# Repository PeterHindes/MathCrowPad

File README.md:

# MathCrowPad

## The MathCrowPad is a numberpad for chemistry, math, and spreadsheets.

Its main three features are:
 * Two knobs to scroll through spreadsheets
 * An oled screen to show guides for the knobs
 * An extra row for parenthisis(), exponent^, factorial!, latex syntax$$ etc.

Feel free to make up to 10 for personal use.

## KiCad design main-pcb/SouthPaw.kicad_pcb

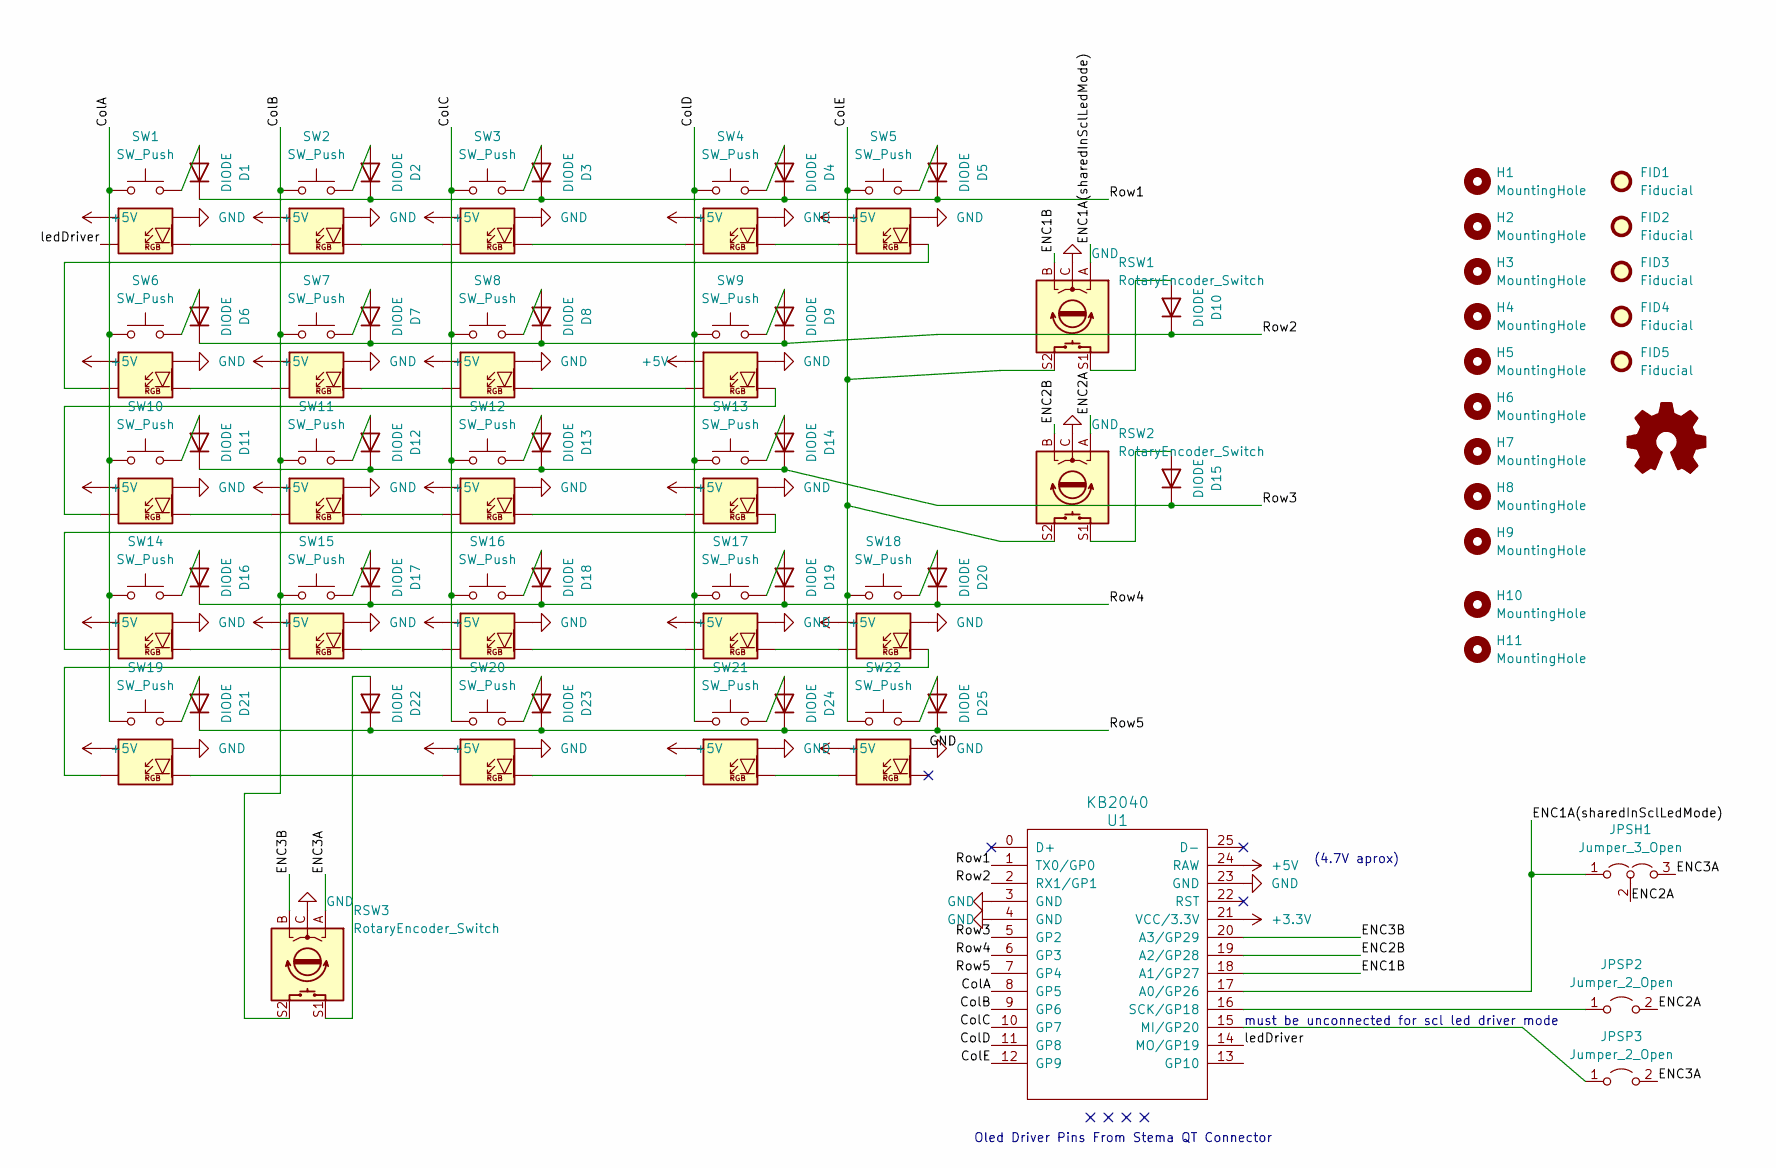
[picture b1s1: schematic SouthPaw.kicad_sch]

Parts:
D1, D2, D3, D4, D5, D6, D7, D8, D9, D10, D11, D12, D13, D14, D15, D16, D17, D18, D19, D20, D21, D22, D23, D24, D25: DIODE; Diode-dual
FID1, FID2, FID3, FID4, FID5: Fiducial; Fiducial_0.5mm_Mask1mm
H1: MountingHole; 0.91in 128x32 I2C STEMMA QT standoff only with cutout
H2, H3, H4, H5, H6, H7, H8, H9, H10, H11: MountingHole; m2.5 hole
JPSH1: Jumper_3_Open; SolderJumper-3_P2.0mm_Open_TrianglePad1.0x1.5mm
JPSP2, JPSP3: Jumper_2_Open; SolderJumper-2_P1.3mm_Open_TrianglePad1.0x1.5mm
RSW1, RSW2, RSW3: RotaryEncoder_Switch; RotaryEncoder_EC11
SW1, SW2, SW3, SW4, SW5, SW6, SW7, SW8, SW9, SW10, SW11, SW12, SW13, SW14, SW15, SW16, SW17, SW19, SW21: SW_Push; SW_Cherry_MX_1.00u_PCB_WITH_SK6812MINI-E
SW18, SW20, SW22: SW_Push; SW_Cherry_MX_2.00u_PCB_WITH_SK6812MINI-E
U1: KB2040; KB2040 through hole only (top mount with hotpins 3d model v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

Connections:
+3.3V: U1.21 (VCC/3.3V)
+5V: SW1.21 (ledVDD), SW2.21 (ledVDD), SW3.21 (ledVDD), SW4.21 (ledVDD), SW5.21 (ledVDD), SW6.21 (ledVDD), SW7.21 (ledVDD), SW8.21 (ledVDD), SW9.21 (ledVDD), SW10.21 (ledVDD), SW11.21 (ledVDD), SW12.21 (ledVDD), SW13.21 (ledVDD), SW14.21 (ledVDD), SW15.21 (ledVDD), SW16.21 (ledVDD), SW17.21 (ledVDD), SW18.21 (ledVDD), SW19.21 (ledVDD), SW20.21 (ledVDD), SW21.21 (ledVDD), SW22.21 (ledVDD), U1.24 (RAW)
/ColA: SW1.11 (sw1), SW6.11 (sw1), SW10.11 (sw1), SW14.11 (sw1), SW19.11 (sw1), U1.8 (GP5)
/ColB: RSW3.S2, SW2.11 (sw1), SW7.11 (sw1), SW11.11 (sw1), SW15.11 (sw1), U1.9 (GP6)
/ColC: SW3.11 (sw1), SW8.11 (sw1), SW12.11 (sw1), SW16.11 (sw1), SW20.11 (sw1), U1.10 (GP7)
/ColD: SW4.11 (sw1), SW9.11 (sw1), SW13.11 (sw1), SW17.11 (sw1), SW21.11 (sw1), U1.11 (GP8)
/ColE: RSW1.S2, RSW2.S2, SW5.11 (sw1), SW18.11 (sw1), SW22.11 (sw1), U1.12 (GP9)
/ENC1A(sharedInSclLedMode): JPSH1.1 (A), RSW1.A, U1.17 (A0/GP26)
/ENC1B: RSW1.B, U1.18 (A1/GP27)
/ENC2A: JPSH1.2 (C), JPSP2.2 (B), RSW2.A
/ENC2B: RSW2.B, U1.19 (A2/GP28)
/ENC3A: JPSH1.3 (B), JPSP3.2 (B), RSW3.A
/ENC3B: RSW3.B, U1.20 (A3/GP29)
/Row1: D1.2 (K), D2.2 (K), D3.2 (K), D4.2 (K), D5.2 (K), U1.1 (TX0/GP0)
/Row2: D6.2 (K), D7.2 (K), D8.2 (K), D9.2 (K), D10.2 (K), U1.2 (RX1/GP1)
/Row3: D11.2 (K), D12.2 (K), D13.2 (K), D14.2 (K), D15.2 (K), U1.5 (GP2)
/Row4: D16.2 (K), D17.2 (K), D18.2 (K), D19.2 (K), D20.2 (K), U1.6 (GP3)
/Row5: D21.2 (K), D22.2 (K), D23.2 (K), D24.2 (K), D25.2 (K), U1.7 (GP4)
/ledDriver: SW1.24 (ledDIN), U1.14 (MO/GP19)
GND: RSW1.C, RSW2.C, RSW3.C, SW1.23 (ledGND), SW2.23 (ledGND), SW3.23 (ledGND), SW4.23 (ledGND), SW5.23 (ledGND), SW6.23 (ledGND), SW7.23 (ledGND), SW8.23 (ledGND), SW9.23 (ledGND), SW10.23 (ledGND), SW11.23 (ledGND), SW12.23 (ledGND), SW13.23 (ledGND), SW14.23 (ledGND), SW15.23 (ledGND), SW16.23 (ledGND), SW17.23 (ledGND), SW18.23 (ledGND), SW19.23 (ledGND), SW20.23 (ledGND), SW21.23 (ledGND), SW22.23 (ledGND), U1.3 (GND), U1.4 (GND), U1.23 (GND)
unnamed: D1.1 (A), SW1.12 (sw2)
unnamed: D2.1 (A), SW2.12 (sw2)
unnamed: D3.1 (A), SW3.12 (sw2)
unnamed: D4.1 (A), SW4.12 (sw2)
unnamed: D5.1 (A), SW5.12 (sw2)
unnamed: D6.1 (A), SW6.12 (sw2)
unnamed: D7.1 (A), SW7.12 (sw2)
unnamed: D8.1 (A), SW8.12 (sw2)
unnamed: D9.1 (A), SW9.12 (sw2)
unnamed: D10.1 (A), RSW1.S1
unnamed: D11.1 (A), SW10.12 (sw2)
unnamed: D12.1 (A), SW11.12 (sw2)
unnamed: D13.1 (A), SW12.12 (sw2)
unnamed: D14.1 (A), SW13.12 (sw2)
unnamed: D15.1 (A), RSW2.S1
unnamed: D16.1 (A), SW14.12 (sw2)
unnamed: D17.1 (A), SW15.12 (sw2)
unnamed: D18.1 (A), SW16.12 (sw2)
unnamed: D19.1 (A), SW17.12 (sw2)
unnamed: D20.1 (A), SW18.12 (sw2)
unnamed: D21.1 (A), SW19.12 (sw2)
unnamed: D22.1 (A), RSW3.S1
unnamed: D23.1 (A), SW20.12 (sw2)
unnamed: D24.1 (A), SW21.12 (sw2)
unnamed: D25.1 (A), SW22.12 (sw2)
unnamed: JPSP2.1 (A), U1.16 (SCK/GP18)
unnamed: JPSP3.1 (A), U1.15 (MI/GP20)
unnamed: SW1.22 (ledDOUT), SW2.24 (ledDIN)
unnamed: SW2.22 (ledDOUT), SW3.24 (ledDIN)
unnamed: SW3.22 (ledDOUT), SW4.24 (ledDIN)
unnamed: SW4.22 (ledDOUT), SW5.24 (ledDIN)
unnamed: SW5.22 (ledDOUT), SW6.24 (ledDIN)
unnamed: SW6.22 (ledDOUT), SW7.24 (ledDIN)
unnamed: SW7.22 (ledDOUT), SW8.24 (ledDIN)
unnamed: SW8.22 (ledDOUT), SW9.24 (ledDIN)
unnamed: SW10.22 (ledDOUT), SW11.24 (ledDIN)
unnamed: SW9.22 (ledDOUT), SW10.24 (ledDIN)
unnamed: SW11.22 (ledDOUT), SW12.24 (ledDIN)
unnamed: SW12.22 (ledDOUT), SW13.24 (ledDIN)
unnamed: SW13.22 (ledDOUT), SW14.24 (ledDIN)
unnamed: SW14.22 (ledDOUT), SW15.24 (ledDIN)
unnamed: SW15.22 (ledDOUT), SW16.24 (ledDIN)
unnamed: SW16.22 (ledDOUT), SW17.24 (ledDIN)
unnamed: SW17.22 (ledDOUT), SW18.24 (ledDIN)
unnamed: SW18.22 (ledDOUT), SW19.24 (ledDIN)
unnamed: SW19.22 (ledDOUT), SW20.24 (ledDIN)
unnamed: SW20.22 (ledDOUT), SW21.24 (ledDIN)
unnamed: SW21.22 (ledDOUT), SW22.24 (ledDIN)

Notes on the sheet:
Oled Driver Pins From Stema QT Connector
must be unconnected for scl led driver mode
(4.7V aprox)

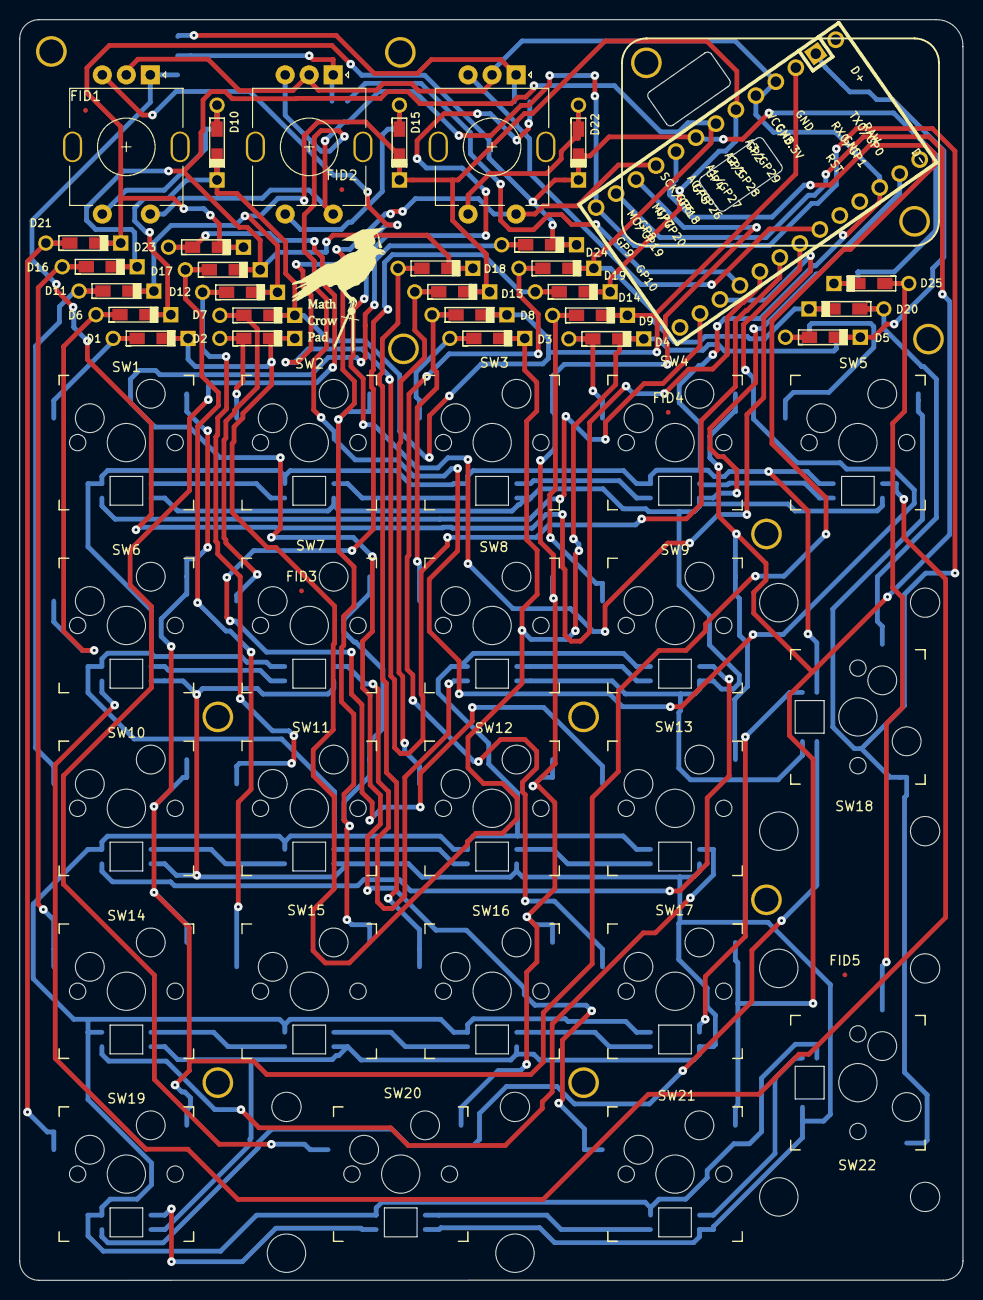
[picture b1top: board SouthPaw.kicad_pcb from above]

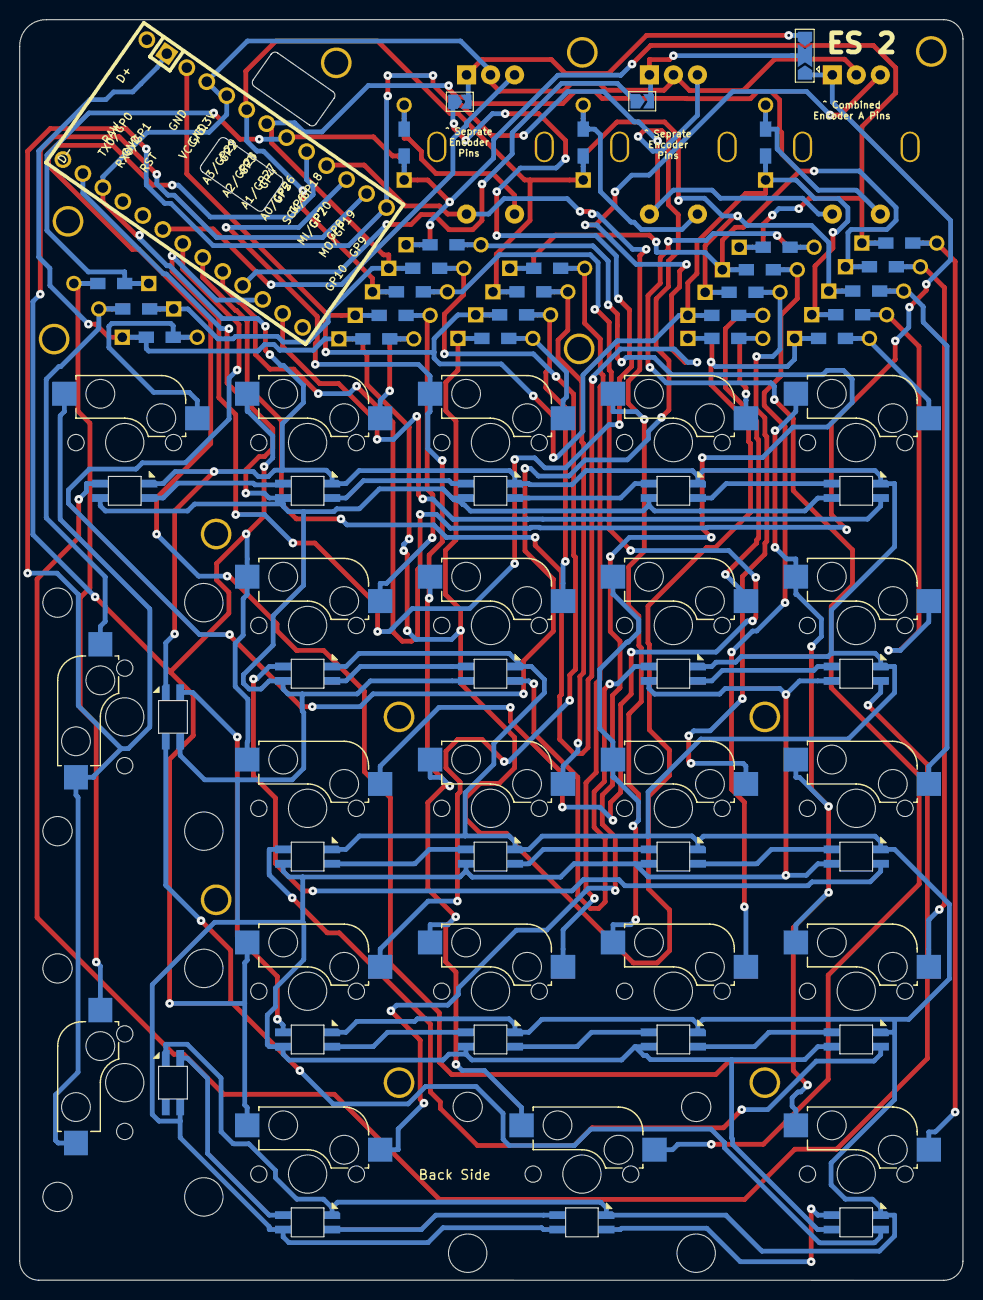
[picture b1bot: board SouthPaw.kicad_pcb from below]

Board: 2 copper layers, 98.2 x 131.3 mm, 70 parts (3 on the bottom side), 67 nets.

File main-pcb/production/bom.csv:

Designator,Footprint,Quantity,Value,LCSC Part #
"D1, D10, D11, D12, D13, D14, D15, D16, D17, D18, D19, D2, D20, D21, D22, D23, D24, D25, D3, D4, D5, D6, D7, D8, D9",Diode-dual,25,DIODE,
FID1,Fiducial_0.5mm_Mask1mm,1,Fiducial,
JPSH1,SolderJumper-3_P2.0mm_Open_TrianglePad1.0x1.5mm,1,Jumper_3_Open,
"JPSP2, JPSP3",SolderJumper-2_P1.3mm_Open_TrianglePad1.0x1.5mm,2,Jumper_2_Open,
"RSW1, RSW2, RSW3",RotaryEncoder_EC11,3,RotaryEncoder_Switch,
"SW1, SW10, SW11, SW12, SW13, SW14, SW15, SW16, SW17, SW19, SW2, SW21, SW3, SW4, SW5, SW6, SW7, SW8, SW9",SW_Cherry_MX_1.00u_PCB_WITH_SK6812MINI-E,19,SW_Push,
"SW18, SW20, SW22",SW_Cherry_MX_2.00u_PCB_WITH_SK6812MINI-E,3,SW_Push,
U1,KB2040 through hole only (top mount with hotpins 3d model view),1,KB2040,

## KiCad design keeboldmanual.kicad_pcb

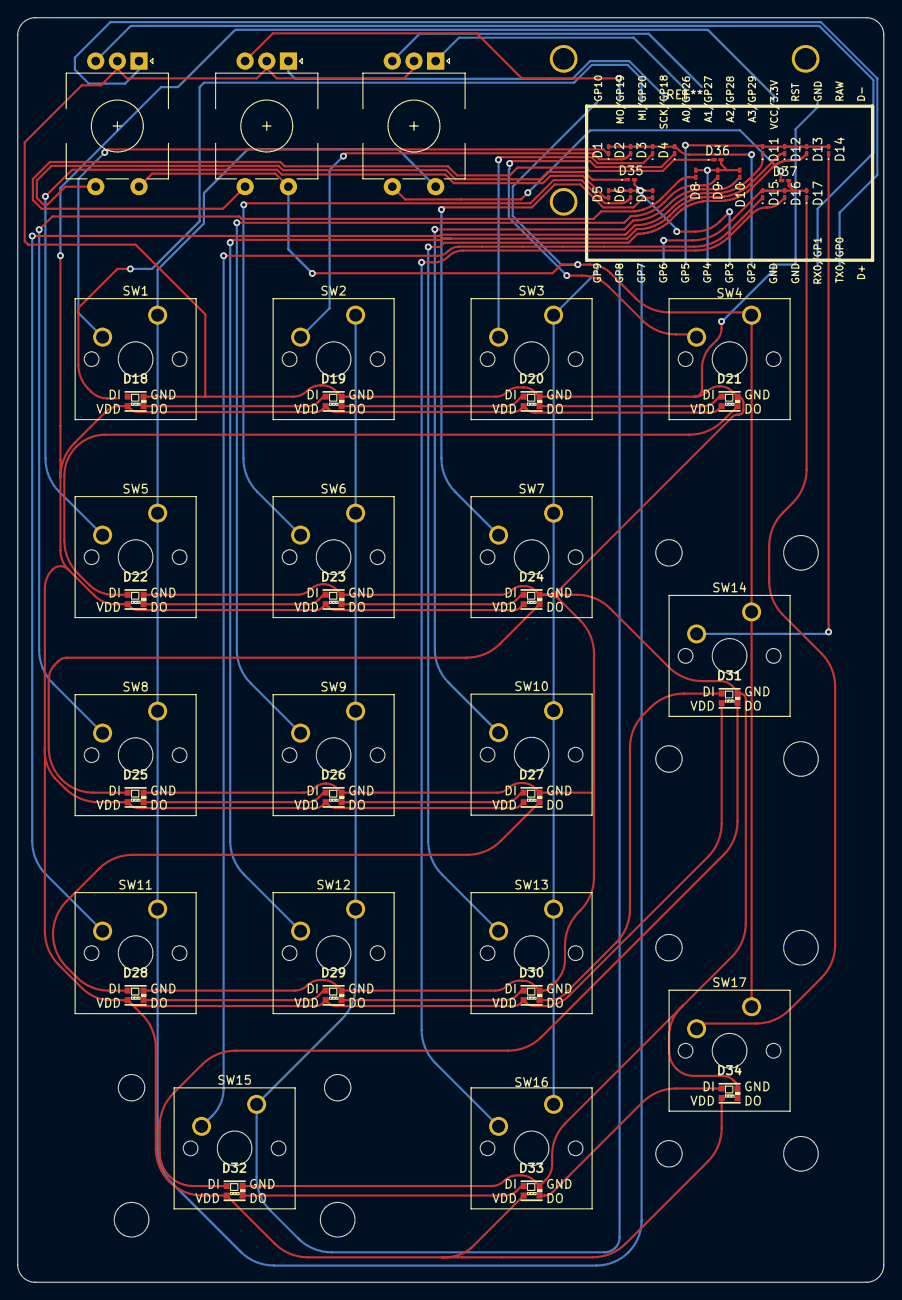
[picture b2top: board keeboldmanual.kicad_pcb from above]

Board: 2 copper layers, 100.0 x 146.0 mm, 58 parts (1 on the bottom side), 54 nets.

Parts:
D1, D2, D3, D4, D5, D6, D7, D8, D9, D10, D11, D12, D13, D14, D15, D16, D17, D35, D36, D37: DIODE; D_0201_0603Metric_Pad0.64x0.40mm_HandSolder
D18, D19, D20, D21, D22, D23, D24, D25, D26, D27, D28, D29, D30, D31, D32, D33, D34: WS2812B_2mm; WS2812B 2mmx2.2mm version
SW1, SW2, SW3, SW4, SW5, SW6, SW7, SW8, SW9, SW10, SW11, SW12, SW13, SW16: SW_Push; SW_Cherry_MX_1.00u_PCB
SW14, SW17: SW_Push; SW_Cherry_MX_2.00u_Vertical_PCB
SW15: SW_Push; SW_Cherry_MX_2.00u_PCB
SW18, SW19, SW20: RotaryEncoder_Switch; RotaryEncoder_EC11
U1: KB2040; KB2040 (modified from Elite-C-castellated-24pin)

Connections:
/3.3V: D18.4 (VDD), D19.4 (VDD), D20.4 (VDD), D21.4 (VDD), D22.4 (VDD), D23.4 (VDD), D24.4 (VDD), D25.4 (VDD), D26.4 (VDD), D27.4 (VDD), D28.4 (VDD), D29.4 (VDD), D30.4 (VDD), D31.4 (VDD), D32.4 (VDD), D33.4 (VDD), D34.4 (VDD), U1.21 (VCC/3.3V)
/GND: D18.2 (GND), D19.2 (GND), D20.2 (GND), D21.2 (GND), D22.2 (GND), D23.2 (GND), D24.2 (GND), D25.2 (GND), D26.2 (GND), D27.2 (GND), D28.2 (GND), D29.2 (GND), D30.2 (GND), D31.2 (GND), D32.2 (GND), D33.2 (GND), D34.2 (GND), SW18.C, SW19.C, SW20.C, U1.3 (GND), U1.4 (GND), U1.23 (GND)
unnamed: D1.1 (A), SW1.2
unnamed: D1.2 (K), D2.2 (K), D3.2 (K), D4.2 (K), U1.5 (GP2)
unnamed: D2.1 (A), SW2.2
unnamed: D3.1 (A), SW3.2
unnamed: D4.1 (A), SW4.2
unnamed: D5.1 (A), SW5.2
unnamed: D5.2 (K), D6.2 (K), D7.2 (K), D35.2 (K), U1.6 (GP3)
unnamed: D6.1 (A), SW6.2
unnamed: D7.1 (A), SW7.2
unnamed: D8.1 (A), SW8.2
unnamed: D9.1 (A), SW9.2
unnamed: D10.1 (A), SW10.2
unnamed: D8.2 (K), D9.2 (K), D10.2 (K), D36.2 (K), U1.7 (GP4)
unnamed: D11.1 (A), SW11.2
unnamed: D11.2 (K), D12.2 (K), D13.2 (K), D14.2 (K), U1.8 (GP5)
unnamed: D12.1 (A), SW12.2
unnamed: D13.1 (A), SW13.2
unnamed: D14.1 (A), SW14.2
unnamed: D15.1 (A), SW15.2
unnamed: D15.2 (K), D16.2 (K), D17.2 (K), D37.2 (K), U1.9 (GP6)
unnamed: D16.1 (A), SW16.2
unnamed: D17.1 (A), SW17.2
unnamed: D18.1 (DOUT), D19.3 (DIN)
unnamed: D18.3 (DIN), U1.15 (MI/GP20)
unnamed: D19.1 (DOUT), D20.3 (DIN)
unnamed: D20.1 (DOUT), D21.3 (DIN)
unnamed: D21.1 (DOUT), D22.3 (DIN)
unnamed: D22.1 (DOUT), D23.3 (DIN)
unnamed: D23.1 (DOUT), D24.3 (DIN)
unnamed: D24.1 (DOUT), D25.3 (DIN)
unnamed: D25.1 (DOUT), D26.3 (DIN)
unnamed: D26.1 (DOUT), D27.3 (DIN)
unnamed: D27.1 (DOUT), D28.3 (DIN)
unnamed: D28.1 (DOUT), D29.3 (DIN)
unnamed: D29.1 (DOUT), D30.3 (DIN)
unnamed: D30.1 (DOUT), D31.3 (DIN)
unnamed: D31.1 (DOUT), D32.3 (DIN)
unnamed: D32.1 (DOUT), D33.3 (DIN)
unnamed: D33.1 (DOUT), D34.3 (DIN)
unnamed: D35.1 (A), SW18.S1
unnamed: D36.1 (A), SW19.S1
unnamed: D37.1 (A), SW20.S1
unnamed: SW1.1, SW5.1, SW8.1, SW11.1, SW20.S2, U1.10 (GP7)
unnamed: SW3.1, SW7.1, SW10.1, SW13.1, SW16.1, U1.12 (GP9)
unnamed: SW2.1, SW6.1, SW9.1, SW12.1, SW15.1, U1.11 (GP8)
unnamed: SW4.1, SW14.1, SW17.1, SW18.S2, SW19.S2, U1.13 (GP10)
unnamed: SW18.A, U1.1 (TX0/GP0)
unnamed: SW18.B, U1.2 (RX1/GP1)
unnamed: SW19.A, U1.16 (SCK/GP18)
unnamed: SW19.B, U1.14 (MO/GP19)
unnamed: SW20.A, U1.17 (A0/GP26)
unnamed: SW20.B, U1.18 (A1/GP27)

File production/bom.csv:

Designator,Footprint,Quantity,Value,LCSC Part #
RSW3,RotaryEncoder_EC11,1,RotaryEncoder_Switch,
RSW1,RotaryEncoder_EC11,1,RotaryEncoder_Switch,
RSW2,RotaryEncoder_EC11,1,RotaryEncoder_Switch,
SW18,SW_Cherry_MX_2.00u_PCB_WITH_SK6812MINI-E,1,SW_Push,
SW22,SW_Cherry_MX_2.00u_PCB_WITH_SK6812MINI-E,1,SW_Push,
SW20,SW_Cherry_MX_2.00u_PCB_WITH_SK6812MINI-E,1,SW_Push,
SW3,SW_Cherry_MX_1.00u_PCB_WITH_SK6812MINI-E,1,SW_Push,
SW11,SW_Cherry_MX_1.00u_PCB_WITH_SK6812MINI-E,1,SW_Push,
SW1,SW_Cherry_MX_1.00u_PCB_WITH_SK6812MINI-E,1,SW_Push,
SW15,SW_Cherry_MX_1.00u_PCB_WITH_SK6812MINI-E,1,SW_Push,
SW4,SW_Cherry_MX_1.00u_PCB_WITH_SK6812MINI-E,1,SW_Push,
SW16,SW_Cherry_MX_1.00u_PCB_WITH_SK6812MINI-E,1,SW_Push,
SW8,SW_Cherry_MX_1.00u_PCB_WITH_SK6812MINI-E,1,SW_Push,
SW5,SW_Cherry_MX_1.00u_PCB_WITH_SK6812MINI-E,1,SW_Push,
SW6,SW_Cherry_MX_1.00u_PCB_WITH_SK6812MINI-E,1,SW_Push,
SW12,SW_Cherry_MX_1.00u_PCB_WITH_SK6812MINI-E,1,SW_Push,
SW10,SW_Cherry_MX_1.00u_PCB_WITH_SK6812MINI-E,1,SW_Push,
SW7,SW_Cherry_MX_1.00u_PCB_WITH_SK6812MINI-E,1,SW_Push,
SW2,SW_Cherry_MX_1.00u_PCB_WITH_SK6812MINI-E,1,SW_Push,
SW13,SW_Cherry_MX_1.00u_PCB_WITH_SK6812MINI-E,1,SW_Push,
SW17,SW_Cherry_MX_1.00u_PCB_WITH_SK6812MINI-E,1,SW_Push,
SW9,SW_Cherry_MX_1.00u_PCB_WITH_SK6812MINI-E,1,SW_Push,
SW14,SW_Cherry_MX_1.00u_PCB_WITH_SK6812MINI-E,1,SW_Push,
SW21,SW_Cherry_MX_1.00u_PCB_WITH_SK6812MINI-E,1,SW_Push,
SW19,SW_Cherry_MX_1.00u_PCB_WITH_SK6812MINI-E,1,SW_Push,
D16,Diode-dual,1,DIODE,
D13,Diode-dual,1,DIODE,
D4,Diode-dual,1,DIODE,
D21,Diode-dual,1,DIODE,
D18,Diode-dual,1,DIODE,
D1,Diode-dual,1,DIODE,
D9,Diode-dual,1,DIODE,
D6,Diode-dual,1,DIODE,
D11,Diode-dual,1,DIODE,
D3,Diode-dual,1,DIODE,
D5,Diode-dual,1,DIODE,
D24,Diode-dual,1,DIODE,
D25,Diode-dual,1,DIODE,
D20,Diode-dual,1,DIODE,
D23,Diode-dual,1,DIODE,
D14,Diode-dual,1,DIODE,
STA2,m2.5 hole,1,m2.5 hole,
D10,Diode-dual,1,DIODE,
D15,Diode-dual,1,DIODE,
D22,Diode-dual,1,DIODE,
D2,Diode-dual,1,DIODE,
STA1,0.91in 128x32 I2C STEMMA QT standoff only,1,0.91in 128x32 I2C STEMMA QT standoff only,
D17,Diode-dual,1,DIODE,
D12,Diode-dual,1,DIODE,
D8,Diode-dual,1,DIODE,
D7,Diode-dual,1,DIODE,
D19,Diode-dual,1,DIODE,
U1,KB2040 through hole hybrid (modified from Elite-C-castellated-24pin-holes),1,KB2040,
STA7,,1,,
STA6,,1,,
STA3,,1,,
STA5,,1,,
STA4,,1,,

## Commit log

2022-09-18 fix missing libraries
    might have issues with the outdated keebio components repo might need to fork
2022-09-18 Update keebio-components
2022-09-18 Cleanup My Mess
2022-09-18 Part one of footprint cleanup
2022-09-18 Making progress
2022-09-19 Start on plate cad
2022-09-19 Update PeteCB-Kicad-Library
2022-09-19 Complete Switch plate
    Fitment testes still needed
2022-09-21 more progress with switch plate
2022-10-06 fixed pinnouts
    rotary encoders now all share a common a pin
2022-10-07 Some work on traces (drc errors present)
2022-10-07 fixed schematic errors
2022-10-15 routing underway
2022-10-22 I think Im finished with es2
2022-10-23 added clarity to schematic that does not change electrical
2022-10-27 New Logo New Name
2022-10-27 Logo inserted without vias below
2023-01-02 update depends
2023-01-03 Some mech cad progress
2023-01-07 l block failure
2023-01-16 more notes
